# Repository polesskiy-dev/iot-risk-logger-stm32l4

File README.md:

# IoT Risk Data Logger, 
## STM32L4 based

Open source & open hardware project aimed to collect environment data e.g for logistics, cold chain monitoring, last mile delivery, etc.

## Features
TODO

## Firmware docs

[Documentation: Doxygen](https://polesskiy-dev.github.io/iot-risk-logger-stm32l4/)

## Firmware structure
* enclosure - 3D models for enclosure
* hardware - schematics, PCB, BOM
* firmware/iot-risk-logger-stm32l4 - main application
  * libraries - external libraries
  * [app](https://github.com/polesskiy-dev/iot-risk-logger-stm32l4/tree/main/firmware/iot-risk-logger-stm32l4/app) - main application
    * drivers - drivers for peripherals
    * core - actors util functions, core non-threaded modules
    * config - configuration files, list of events and actors    
    * [tasks](https://github.com/polesskiy-dev/iot-risk-logger-stm32l4/tree/main/firmware/iot-risk-logger-stm32l4/app/tasks) - main threads

## Parts video 

https://github.com/polesskiy-dev/iot-risk-logger-stm32l4/assets/5185707/393b0768-925d-4c34-bb85-259de904c167

## Schematics & PCB
[Schematics PDF](hardware/docs/iot-risk-logger-stm32l4.pdf)

## Hardware specifications

|Item|Description|
|-|-|
| MCU | STM32L412 Cortex M4, 80MHz (48), 128K ROM, 40K RAM, TQFP32 |
| Crystal | 32.768kHz |
| Flash | QSPI 64Mbit |
| NFC | ST25DV04K |
| Temperature & Humidity | SHT30-DIS |
| Light | OPT3001 |
| IMU | LIS2DW12 |
| Power | CR2032 3V 235mAh |

## Enclosure
### Assembly

### Developed with
|||
|-|-|
| OS | MacOS, Apple Silicon |
| Schematics & PCB | KiCAD 7.0.0 |
| 3D CAD | Fusion 360 |
| Graphical MCU configure | STM32CubeMX 6.10.0 | 
| IDE | neovim, CLion |
| Hardware debug probe | J-Link EDU Mini 8.08.91 |
| Firmware debug | Segger Ozone 7.94 | 
| Firmware debug analysis | Segger SystemView 3.52 |
| Power analysis | Nordic Power Profiler Kit II |
| Oscilloscope & Logic analyzer | Digilent Analog Discovery 3 |
| Logic analyzer software | Digilent Waveforms | 

## Quick start

After clone, init submodules if you forgot

```bash
git submodule update --init --recursive
```

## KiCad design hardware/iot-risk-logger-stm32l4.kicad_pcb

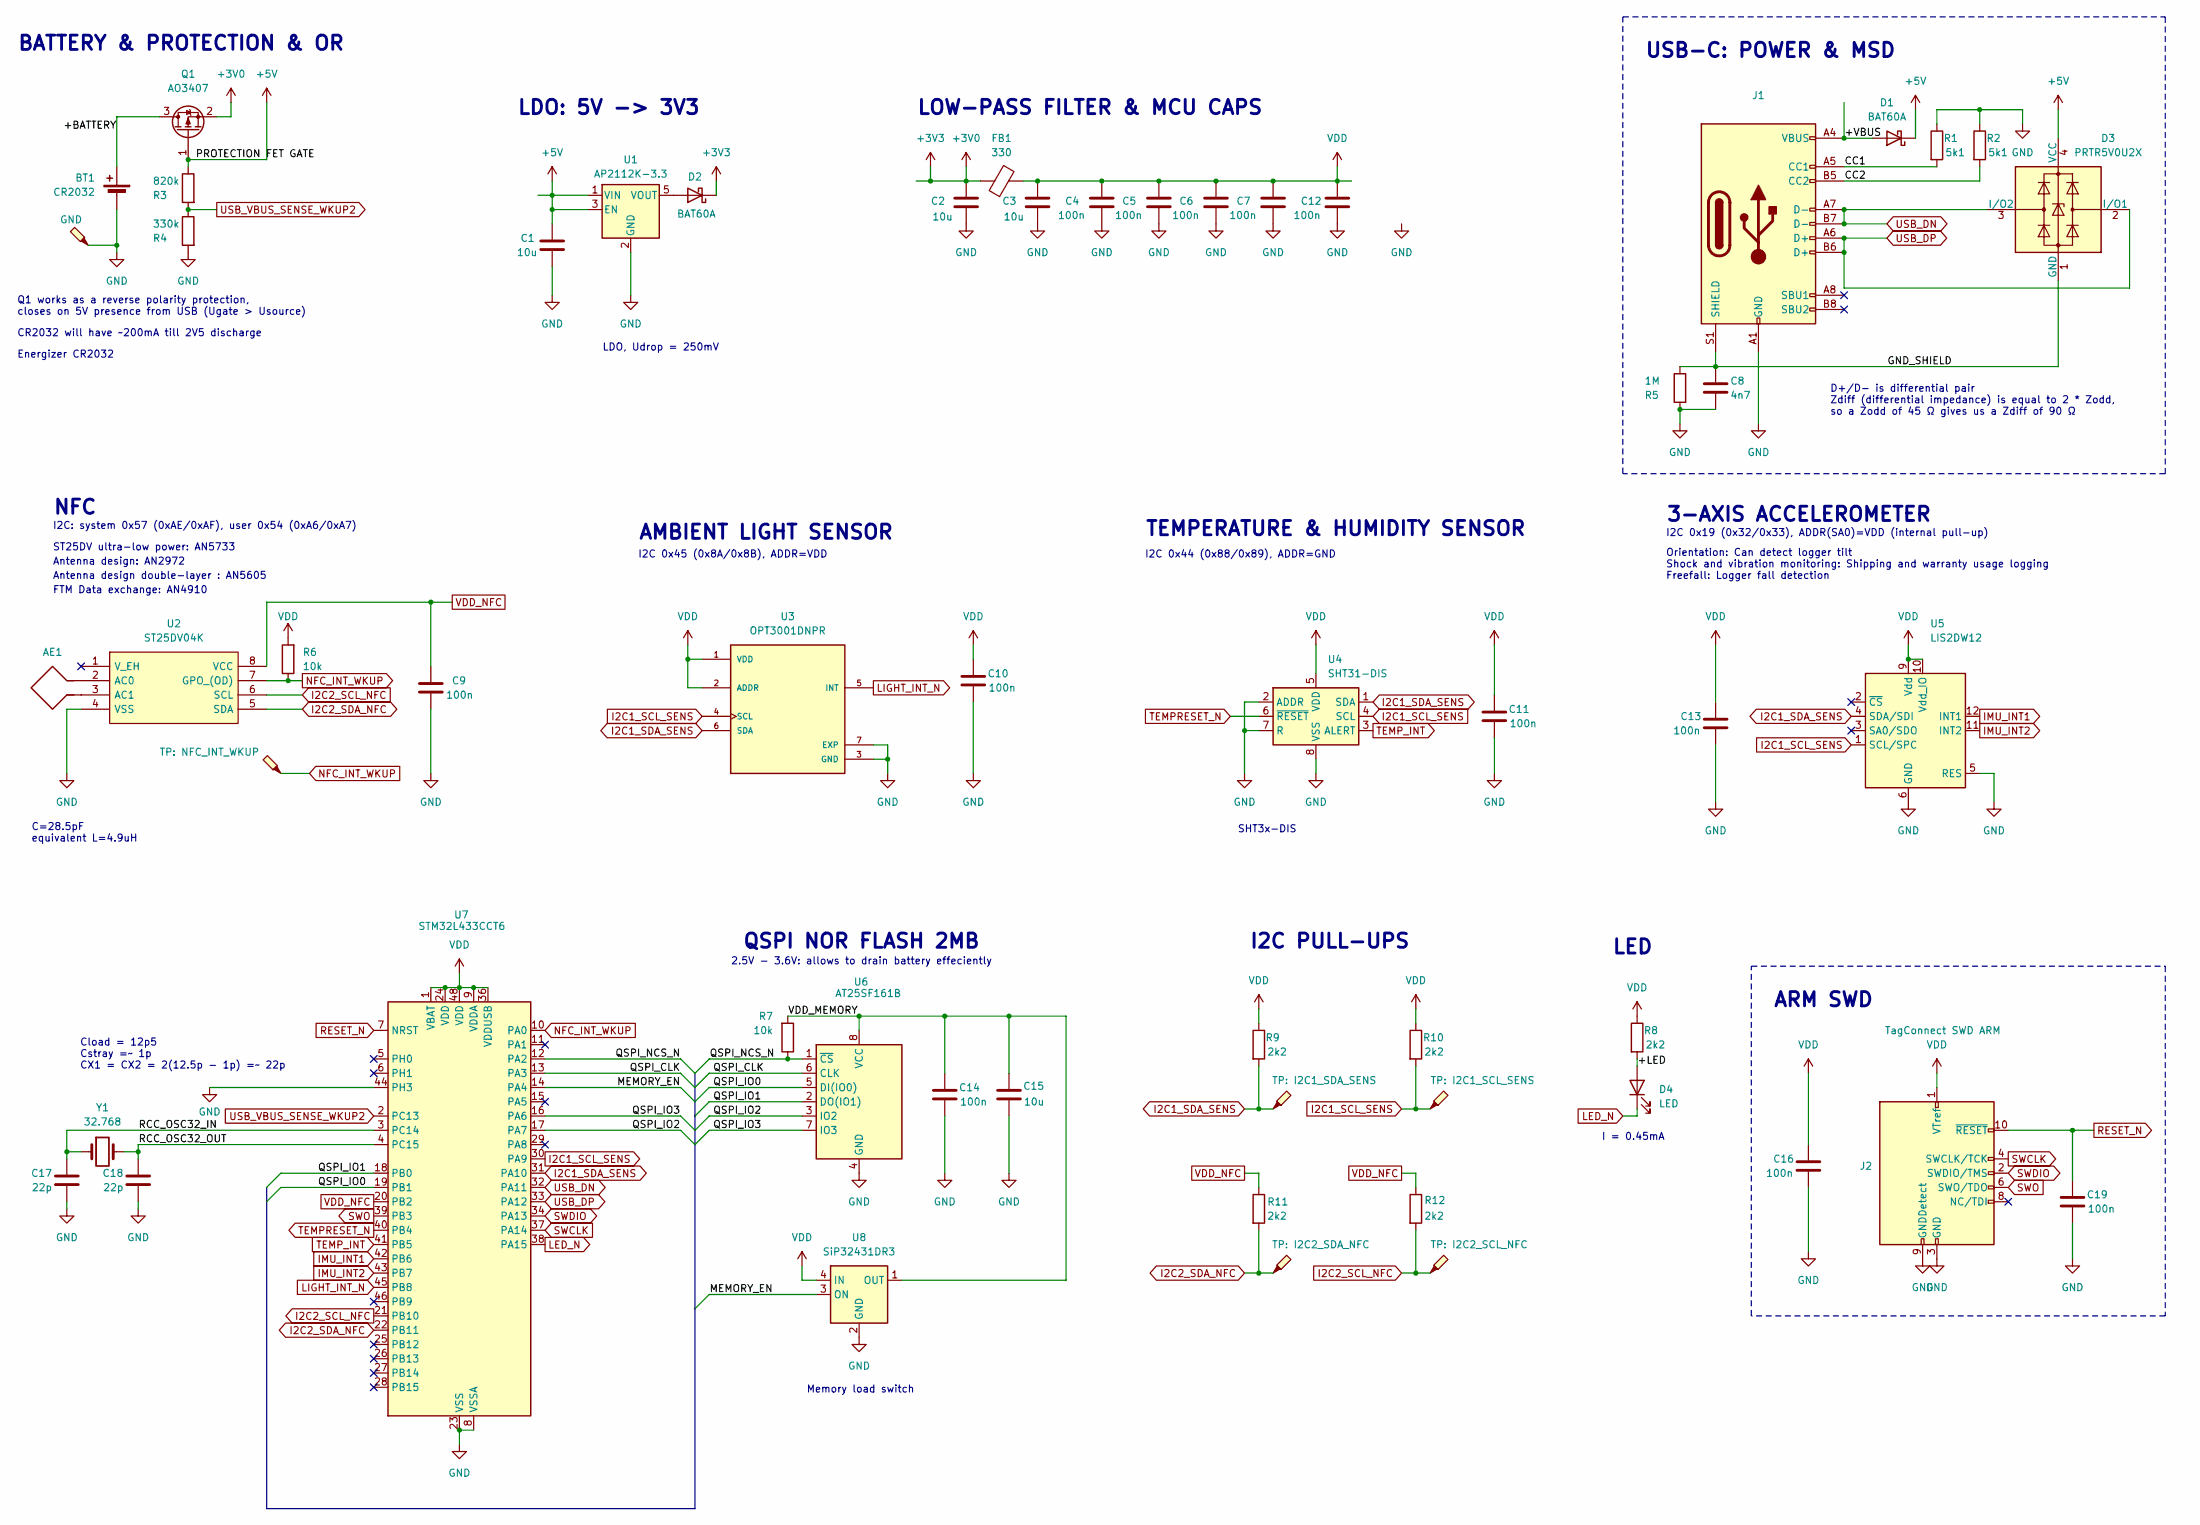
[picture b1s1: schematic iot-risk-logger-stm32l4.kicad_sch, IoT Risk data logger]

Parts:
AE1: Antenna_Loop; NFC_20x40
BT1: CR2032; BatteryHolder_Keystone_3002_1x2032; Mfr. Part # MY-2032-05; LCSC Part # C964829
C1, C2, C3, C15: 10u; C_0805_2012Metric_Pad1.18x1.45mm_HandSolder; Mfr. Part # CL21A106KOQNNNE; LCSC Part # C1713
C4, C5, C6, C7, C9, C10, C11, C12, C13, C14, C16, C19: 100n; C_0603_1608Metric_Pad1.08x0.95mm_HandSolder; Mfr. Part # CL10B104KB8NNNC; LCSC Part # C1591
C8: 4n7; C_0603_1608Metric_Pad1.08x0.95mm_HandSolder; Mfr. Part # CL10B472KB8NNNC; LCSC Part # C1621
C17, C18: 22p; C_0603_1608Metric; Mfr. Part # CL10C220JB8NNNC; LCSC Part # C1653
D1, D2: BAT60A; D_SOD-323_HandSoldering; Mfr. Part # BAT60A; LCSC Part # C5355496
D3: PRTR5V0U2X; SOT-143; Mfr. Part # PRTR5V0U2X; LCSC Part # C2827688
D4: LED; LED_0805_2012Metric_Pad1.15x1.40mm_HandSolder; Mfr. Part # NCD0805G1; LCSC Part # C84260
FB1: 330; L_0805_2012Metric_Pad1.15x1.40mm_HandSolder; Mfr. Part # BLM18SG331TN1D; LCSC Part # C88989
J1: USB Type-C; USB_C_Receptacle_XKB_U262-16XN-4BVC11; Mfr. Part # KH-TYPE-C-16P; LCSC Part # C709357
J2: TagConnect SWD ARM; Tag-Connect_TC2050-IDC-NL_2x05_P1.27mm_Vertical_with_bottom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
Q1: AO3407; SOT-23; Mfr. Part # AO3407; LCSC Part # C2938376
R1, R2: 5k1; R_0603_1608Metric_Pad0.98x0.95mm_HandSolder; Mfr. Part # RC0603JR-075K1L; LCSC Part # C14677
R3: 820k; R_0603_1608Metric_Pad0.98x0.95mm_HandSolder; Mfr. Part # RC0603FR-07820KL; LCSC Part # C141684
R4: 330k; R_0603_1608Metric_Pad0.98x0.95mm_HandSolder; Mfr. Part # RC0603FR-07330KL; LCSC Part # C114618
R5: 1M; R_0603_1608Metric_Pad0.98x0.95mm_HandSolder; Mfr. Part # RC0603JR-071ML; LCSC Part # C107698
R6, R7: 10k; R_0603_1608Metric_Pad0.98x0.95mm_HandSolder; Mfr. Part # RC0603FR-0710KL; LCSC Part # C98220
R8, R9, R10, R11, R12: 2k2; R_0603_1608Metric_Pad0.98x0.95mm_HandSolder; Mfr. Part # RC0603JR-072K2L; LCSC Part # C113303
TP1: GND; TestPoint_Pad_D1.5mm
TP2: TP: NFC_INT_WKUP; TestPoint_Pad_D1.5mm
TP3: TP: I2C1_SDA_SENS; TestPoint_Pad_D1.5mm
TP4: TP: I2C1_SCL_SENS; TestPoint_Pad_D1.5mm
TP5: TP: I2C2_SDA_NFC; TestPoint_Pad_D1.5mm
TP6: TP: I2C2_SCL_NFC; TestPoint_Pad_D1.5mm
U1: AP2112K-3.3; SOT-23-5; Mfr. Part # AP2112K-3.3TRG1; LCSC Part # C51118
U2: ST25DV04K; TSSOP-8_4.4x3mm_P0.65mm; Mfr. Part # ST25DV04K-IER6T3; LCSC Part # C2654816
U3: OPT3001DNPR; SON65P200X200X65-7N; Mfr. Part # OPT3001DNPR; LCSC Part # C90462
U4: SHT31-DIS; Sensirion_DFN-8-1EP_2.5x2.5mm_P0.5mm_EP1.1x1.7mm; Mfr. Part # SHT31-DIS-B2.5kS; LCSC Part # C80862
U5: LIS2DW12; LGA-12_2x2mm_P0.5mm; Mfr. Part # LIS2DW12TR; LCSC Part # C189624
U6: AT25SF161B; SOIC-8_3.9x4.9mm_P1.27mm; Mfr. Part # AT25SF161B-SSHD-B; LCSC Part # C5555633
U7: STM32L433CCT6; LQFP-48_7x7mm_P0.5mm; Mfr. Part # STM32L433CCT6; LCSC Part # C110061
U8: SiP32431DR3; SOT-363_SC-70-6; Mfr. Part # SIP32431DR3-T1GE3; LCSC Part # C141606
Y1: 32.768; Crystal_SMD_EuroQuartz_EQ161-2Pin_3.2x1.5mm; Mfr. Part # SC-32S32.768kHz20PPM12.5pF; LCSC Part # C97606

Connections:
+3V0: C2.1, D2.1 (K), FB1.1, Q1.2 (S)
+5V: C1.1, D1.1 (K), D3.4 (VCC), Q1.1 (G), R3.1, U1.1 (VIN), U1.3 (EN)
/+BATTERY: BT1.1 (+), Q1.3 (D)
/+LED: D4.2 (A), R8.2
/+VBUS: D1.2 (A), J1.A4 (VBUS), J1.A9 (VBUS), J1.B4 (VBUS), J1.B9 (VBUS)
/CC1: J1.A5 (CC1), R1.2
/CC2: J1.B5 (CC2), R2.2
/GND_SHIELD: C8.1, D3.1 (GND), J1.S1 (SHIELD), R5.1
/MEMORY_EN: U7.14 (PA4), U8.3 (ON)
/QSPI_CLK: U6.6 (CLK), U7.13 (PA3)
/QSPI_IO0: U6.5 (DI(IO0)), U7.19 (PB1)
/QSPI_IO1: U6.2 (DO(IO1)), U7.18 (PB0)
/QSPI_IO2: U6.3 (IO2), U7.17 (PA7)
/QSPI_IO3: U6.7 (IO3), U7.16 (PA6)
/QSPI_NCS_N: R7.1, U6.1 (~CS), U7.12 (PA2)
/RCC_OSC32_IN: C17.1, U7.3 (PC14), Y1.1
/RCC_OSC32_OUT: C18.1, U7.4 (PC15), Y1.2
/VDD_MEMORY: C14.1, C15.1, R7.2, U6.8 (VCC), U8.1 (OUT)
GND: BT1.2 (-), C1.2, C2.2, C3.2, C4.2, C5.2, C6.2, C7.2, C8.2, C9.2, C10.2, C11.2, C12.2, C13.2, C14.2, C15.2, C16.2, C17.2, C18.2, C19.2, J1.A1 (GND), J1.A12 (GND), J1.B1 (GND), J1.B12 (GND), J2.3 (GND), J2.5 (GND), J2.9 (GNDDetect), R1.1, R2.1, R4.2, R5.2, TP1.1, U1.2 (GND), U2.4 (VSS), U3.3 (GND), U3.7 (EXP), U4.2 (ADDR), U4.7 (R), U4.8 (VSS), U4.9 (VSS), U5.5 (RES), U5.6 (GND), U5.7 (GND), U5.8 (GND), U6.4 (GND), U7.8 (VSSA), U7.23 (VSS), U7.35 (VSS), U7.44 (PH3), U7.47 (VSS), U8.2 (GND), U8.5 (GND)
I2C1_SCL_SENS: R10.2, TP4.1, U3.4 (SCL), U4.4 (SCL), U5.1 (SCL/SPC), U7.30 (PA9)
I2C1_SDA_SENS: R9.2, TP3.1, U3.6 (SDA), U4.1 (SDA), U5.4 (SDA/SDI), U7.31 (PA10)
I2C2_SCL_NFC: R12.2, TP6.1, U2.6 (SCL), U7.21 (PB10)
I2C2_SDA_NFC: R11.2, TP5.1, U2.5 (SDA), U7.22 (PB11)
IMU_INT1: U5.12 (INT1), U7.42 (PB6)
IMU_INT2: U5.11 (INT2), U7.43 (PB7)
LED_N: D4.1 (K), U7.38 (PA15)
LIGHT_INT_N: U3.5 (INT), U7.45 (PB8)
NFC_INT_WKUP: R6.1, TP2.1, U2.7 (GPO_(OD)), U7.10 (PA0)
unnamed: D2.2 (A), U1.5 (VOUT)
unnamed: AE1.2, U2.2 (AC0)
unnamed: AE1.1, U2.3 (AC1)
RESET_N: C19.1, J2.10 (~RESET), U7.7 (NRST)
SWCLK: J2.4 (SWCLK/TCK), U7.37 (PA14)
SWDIO: J2.2 (SWDIO/TMS), U7.34 (PA13)
SWO: J2.6 (SWO/TDO), U7.39 (PB3)
TEMPRESET_N: U4.6 (~RESET), U7.40 (PB4)
TEMP_INT: U4.3 (ALERT), U7.41 (PB5)
USB_DN: D3.3 (I/O2), J1.A7 (D-), J1.B7 (D-), U7.32 (PA11)
USB_DP: D3.2 (I/O1), J1.A6 (D+), J1.B6 (D+), U7.33 (PA12)
USB_VBUS_SENSE_WKUP2: R3.2, R4.1, U7.2 (PC13)
VDD: C3.1, C4.1, C5.1, C6.1, C7.1, C10.1, C11.1, C12.1, C13.1, C16.1, FB1.2, J2.1 (VTref), R6.2, R8.1, R9.1, R10.1, U3.1 (VDD), U3.2 (ADDR), U4.5 (VDD), U5.9 (Vdd), U5.10 (Vdd_IO), U7.1 (VBAT), U7.9 (VDDA), U7.24 (VDD), U7.36 (VDDUSB), U7.48 (VDD), U8.4 (IN)
VDD_NFC: C9.1, R11.1, R12.1, U2.8 (VCC), U7.20 (PB2)

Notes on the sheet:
BATTERY & PROTECTION & OR
CR2032 will have ~200mA till 2V5 discharge
С=28.5pF equivalent L=4.9uH
TEMPERATURE & HUMIDITY SENSOR
ST25DV ultra-low power: AN5733
LDO, Udrop = 250mV
LED
Q1 works as a reverse polarity protection, closes on 5V presence from USB (Ugate > Usource)
QSPI NOR FLASH 2MB
Antenna design double-layer : AN5605
FTM Data exchange: AN4910
Memory load switch
3-AXIS ACCELEROMETER
D+/D- is differential pair Zdiff (differential impedance) is equal to 2 * Zodd, so a Zodd of 45 Ω gives us a Zdiff of 90 Ω
I2C 0x44 (0x88/0x89), ADDR=GND
2.5V - 3.6V: allows to drain battery effeciently
I2C: system 0x57 (0xAE/0xAF), user 0x54 (0xA6/0xA7)
Antenna design: AN2972
Cload = 12p5 Cstray =~ 1p CX1 = CX2 = 2(12.5p - 1p) =~ 22p
ARM SWD
I2C 0x19 (0x32/0x33), ADDR(SA0)=VDD (internal pull-up)
USB-C: POWER & MSD
AMBIENT LIGHT SENSOR
SHT3x-DIS
Orientation: Can detect logger tilt Shock and vibration monitoring: Shipping and warranty usage logging Freefall: Logger fall detection
I = 0.45mA
I2C 0x45 (0x8A/0x8B), ADDR=VDD
LOW-PASS FILTER & MCU CAPS
I2C PULL-UPS
Energizer CR2032
NFC
LDO: 5V -> 3V3

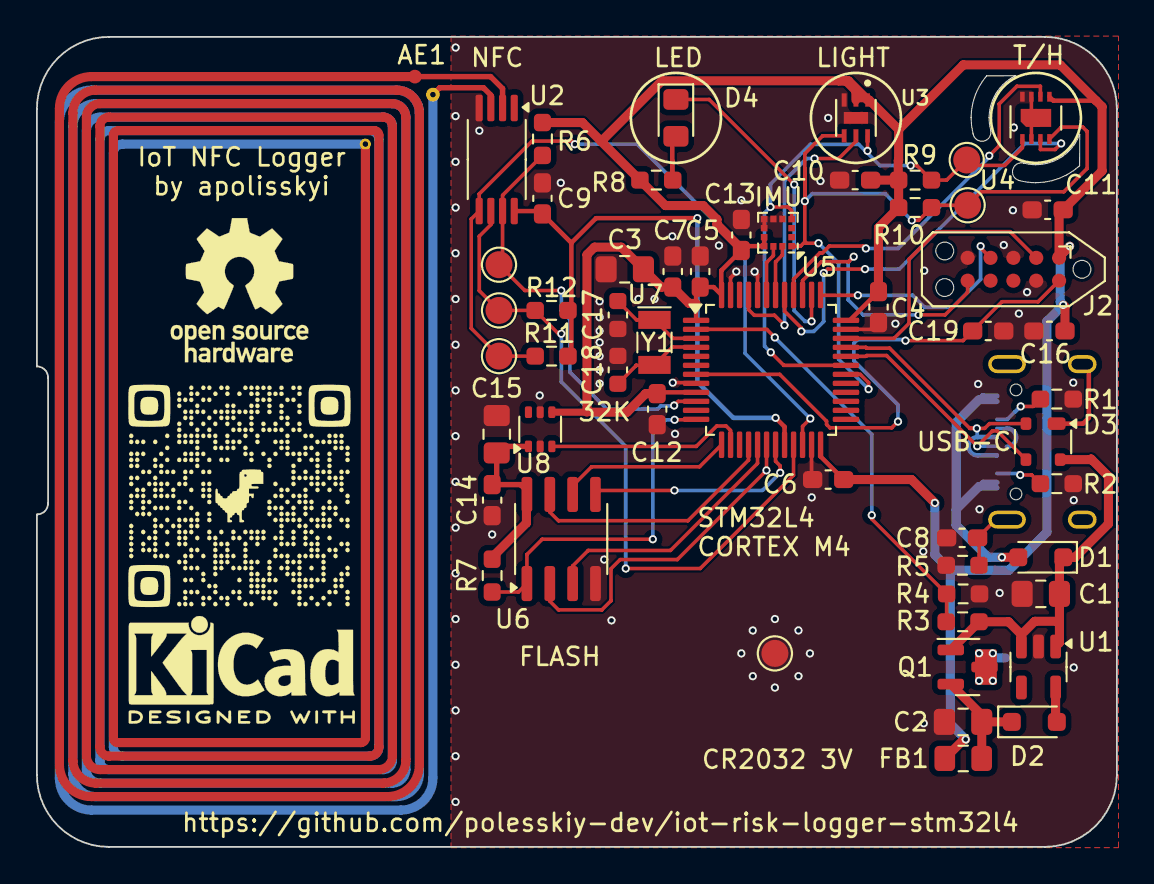
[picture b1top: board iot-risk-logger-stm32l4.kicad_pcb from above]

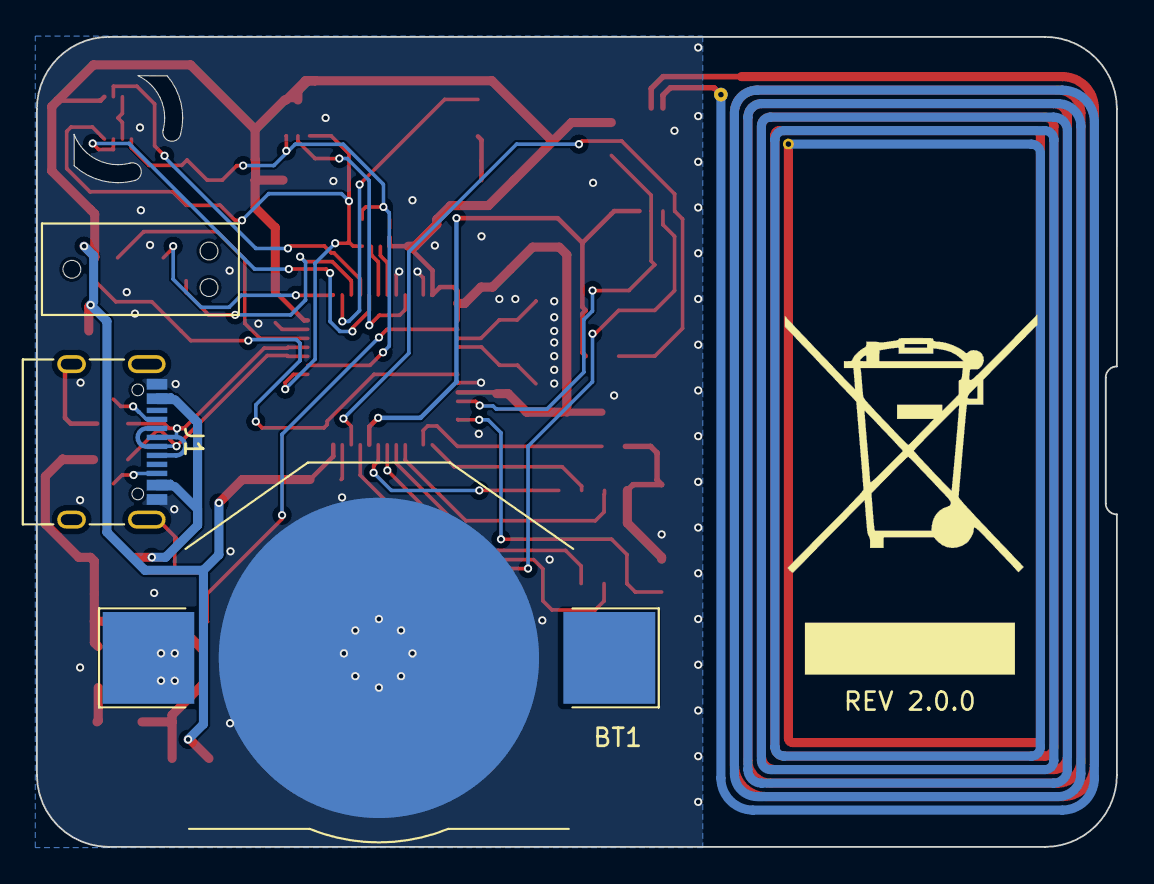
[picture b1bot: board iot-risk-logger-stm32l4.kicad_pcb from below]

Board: 2 copper layers, 60.0 x 45.0 mm, 59 parts (3 on the bottom side), 42 nets.

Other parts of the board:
REF1: KiCad-Logo2_5mm_SilkScreen
REF2: OSHW-Logo_7.5x8mm_SilkScreen
REF3: WEEE-Logo_14x20mm_SilkScreen

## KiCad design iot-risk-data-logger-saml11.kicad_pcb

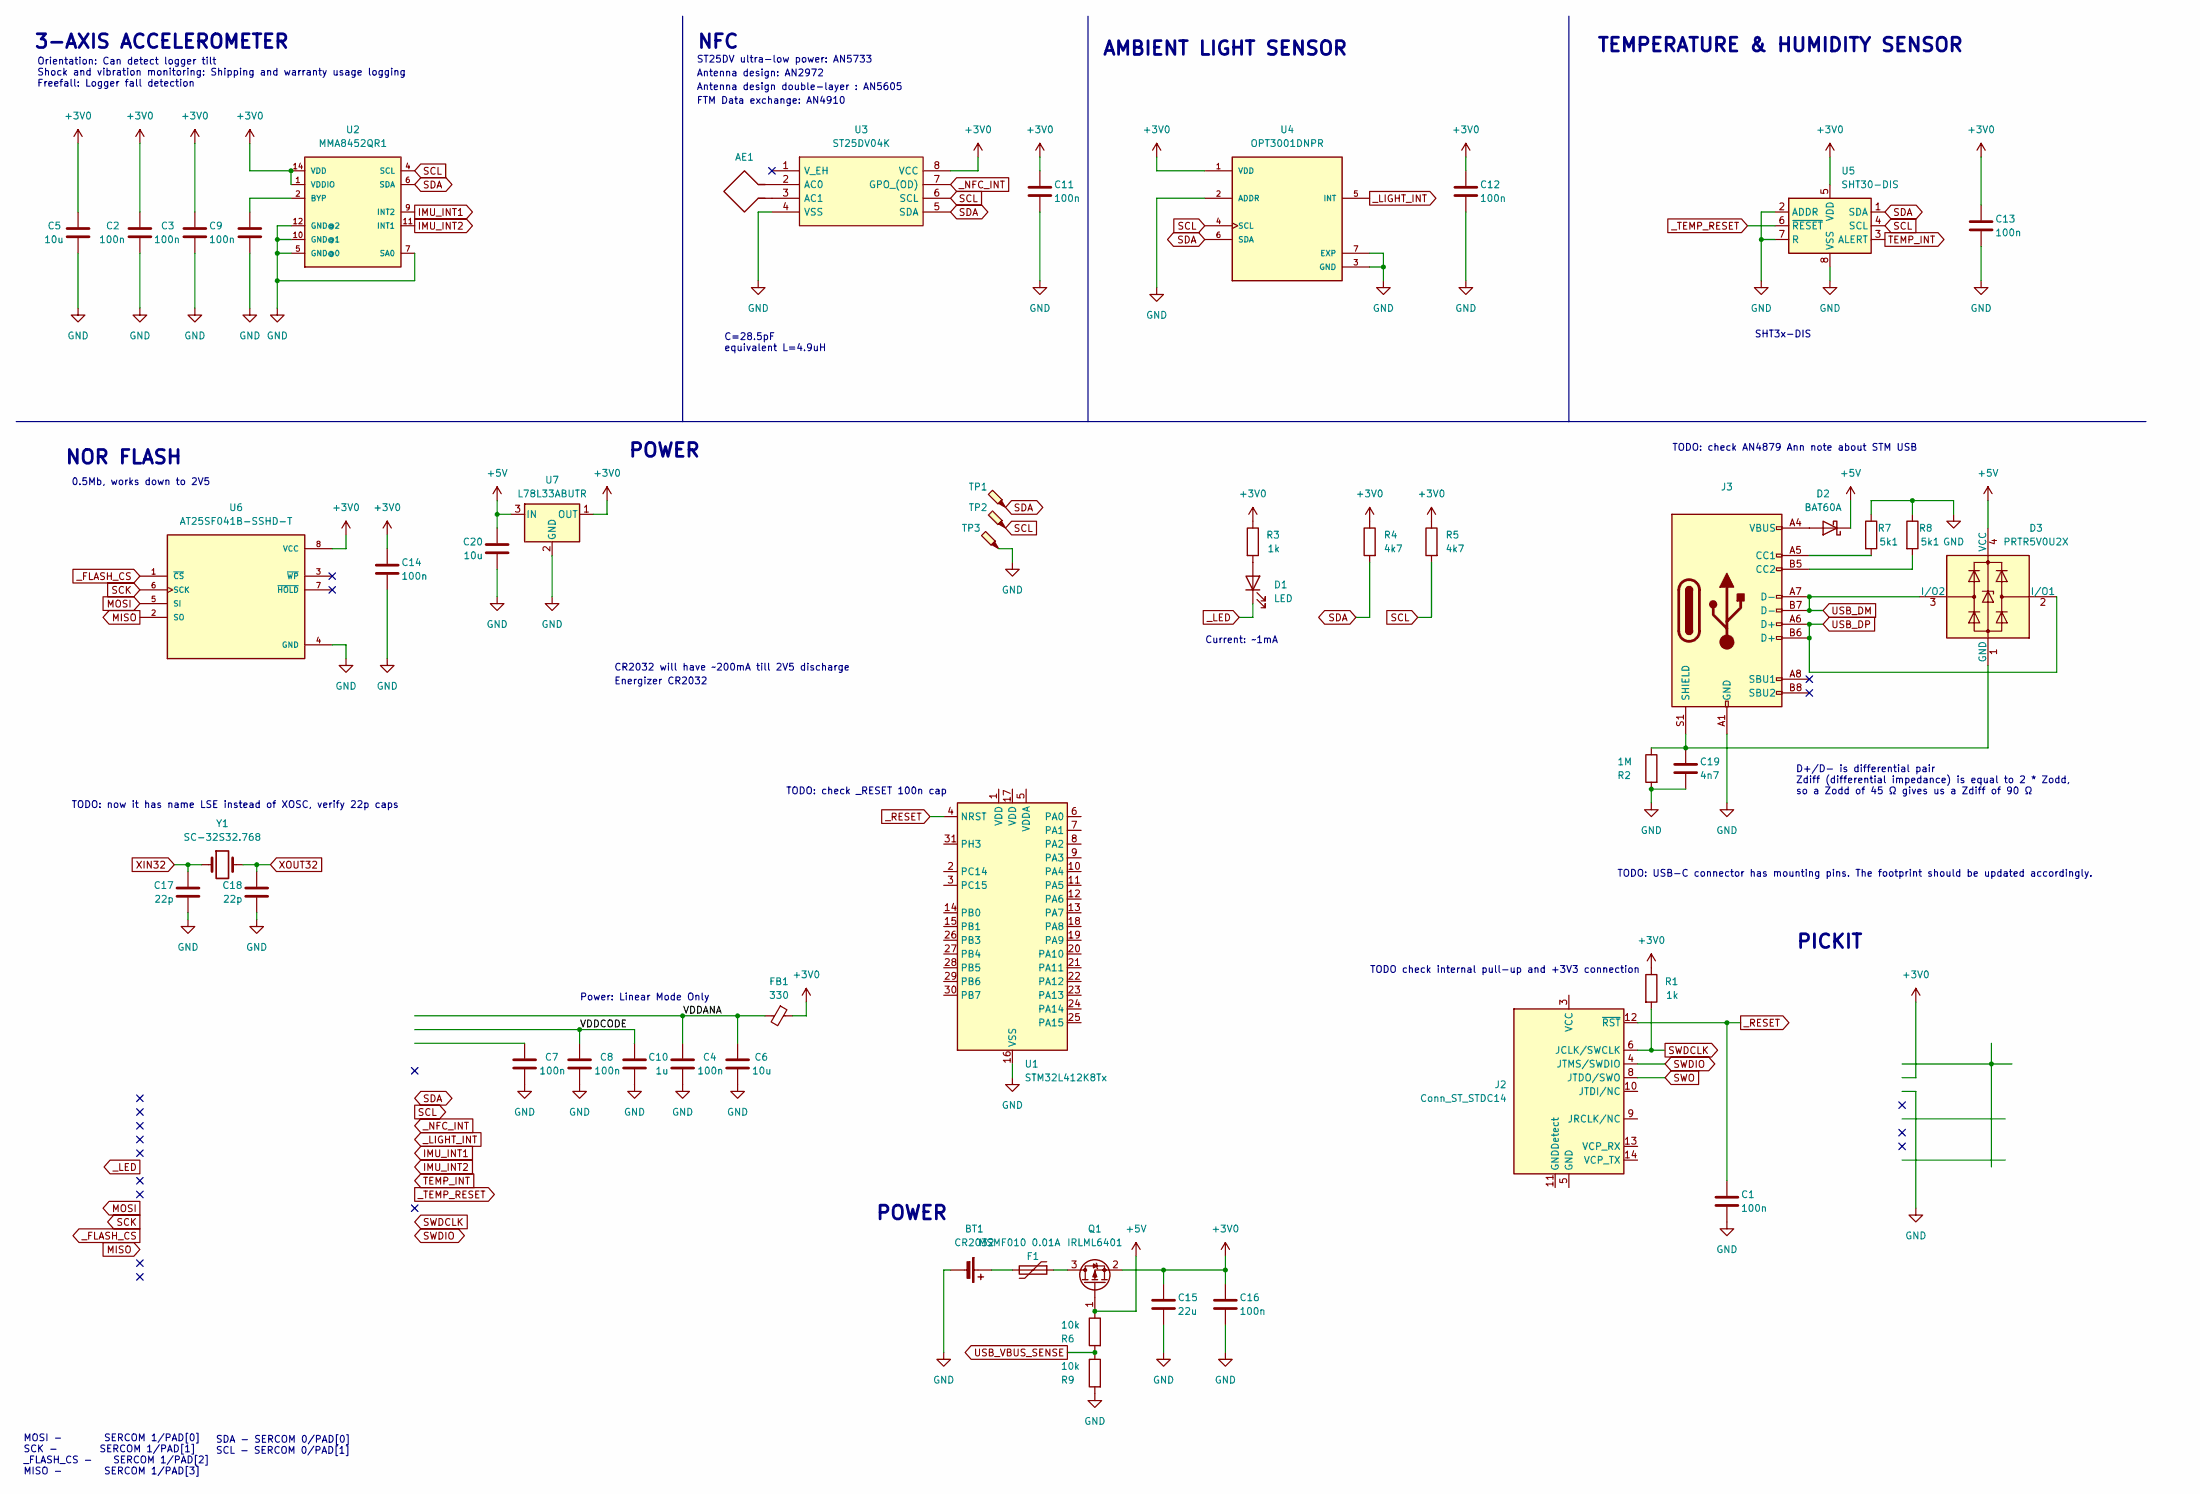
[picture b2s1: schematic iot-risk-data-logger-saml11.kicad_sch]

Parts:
AE1: Antenna_Loop; ANT_NFC_30x40
BT1: CR2032; BatteryHolder_Keystone_3002_1x2032; Part MY-2032-05; LCSC Part C964829
C1, C2, C3, C4, C7, C8, C9, C11, C12, C13, C14, C16: 100n; C_0805_2012Metric_Pad1.18x1.45mm_HandSolder; Part CL21B104KBCNNNC; LCSC Part C1711
C5, C6, C20: 10u; C_0805_2012Metric_Pad1.18x1.45mm_HandSolder; Part CL21A106KOQNNNE; LCSC Part C1713
C10: 1u; C_0805_2012Metric_Pad1.18x1.45mm_HandSolder; Part CL21A105KACLNNC; LCSC Part C2932475
C15: 22u; C_1206_3216Metric_Pad1.33x1.80mm_HandSolder; Part CL31A226KAHNNNE; LCSC Part C12891
C17, C18: 22p; C_0805_2012Metric_Pad1.18x1.45mm_HandSolder; Part CL21C220JBANNNC; LCSC Part C1804
C19: 4n7; C_0805_2012Metric_Pad1.18x1.45mm_HandSolder; Part CL21B472KBANNNC; LCSC Part C50131
D1: LED; LED_0805_2012Metric_Pad1.15x1.40mm_HandSolder; Part NCD0805G1; LCSC Part C84260
D2: BAT60A; D_SOD-323_HandSoldering; Part BAT60A; LCSC Part C5355496
D3: PRTR5V0U2X; SOT-143; Part PRTR5V0U2X; LCSC Part C2827688
F1: MSMF010 0.01A; Fuse_1812_4532Metric_Pad1.30x3.40mm_HandSolder; Part MF-MSMF010-2; LCSC Part C12430
FB1: 330; R_0805_2012Metric_Pad1.20x1.40mm_HandSolder; Part BLM21PG331SN1D; LCSC Part C47130
J2: Conn_ST_STDC14; PinHeader_2x07_P1.27mm_Vertical_SMD
J3: USB Type-C; USB_C_Receptacle_XKB_U262-16XN-4BVC11; Part KH-TYPE-C-16P; LCSC Part C709357
Q1: IRLML6401; SOT-23; Part IRLML6401TRPBF; LCSC Part C3034
R1, R3: 1k; R_0805_2012Metric_Pad1.20x1.40mm_HandSolder; Part RC0805FR-071KL; LCSC Part C95781
R2: 1M; R_0805_2012Metric_Pad1.20x1.40mm_HandSolder; Part RC0805FR-071ML; LCSC Part C107700
R4, R5: 4k7; R_0805_2012Metric_Pad1.20x1.40mm_HandSolder; Part RC0805FR-074K7L; LCSC Part C60816
R6, R9: 10k; R_0805_2012Metric_Pad1.20x1.40mm_HandSolder; Part RC0805FR-0710KL; LCSC Part C84376
R7, R8: 5k1; R_0805_2012Metric_Pad1.20x1.40mm_HandSolder; Part RC0805FR-075K1L; LCSC Part C84375
TP1, TP2, TP3: TestPoint_Probe; TestPoint_THTPad_D1.5mm_Drill0.7mm
U1: STM32L412K8Tx; LQFP-32_7x7mm_P0.8mm
U2: MMA8452QR1; XDCR_MMA8452QR1; Part MMA8452QR1; LCSC Part C11360
U3: ST25DV04K; TSSOP-8_4.4x3mm_P0.65mm; Part ST25DV04K-IER6T3; LCSC Part C2654816
U4: OPT3001DNPR; SON65P200X200X65-7N; Part OPT3001DNPR; LCSC Part C90462
U5: SHT30-DIS; Sensirion_DFN-8-1EP_2.5x2.5mm_P0.5mm_EP1.1x1.7mm; Part SHT30-DIS-B10KS; LCSC Part C2687423
U6: AT25SF041B-SSHD-T; SOIC-8_3.9x4.9mm_P1.27mm; Part AT25SF041B-SSHD-T; LCSC Part C5127618
U7: L78L33ABUTR; SOT-89-3_Handsoldering; Part L78L33ABUTR; LCSC Part C81362
Y1: SC-32S32.768; Crystal_SMD_EuroQuartz_EQ161-2Pin_3.2x1.5mm_HandSoldering; Part SC-32S32.768kHz20PPM12.5pF; LCSC Part C97606

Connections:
+3V0: C2.1, C3.1, C5.1, C11.1, C12.1, C13.1, C14.1, C15.1, C16.1, FB1.1, Q1.2 (S), R1.1, R3.1, R4.1, R5.1, U2.1 (VDDIO), U2.14 (VDD), U3.8 (VCC), U4.1 (VDD), U5.5 (VDD), U6.8 (VCC), U7.1 (OUT)
+5V: C20.1, D2.1 (K), D3.4 (VCC), Q1.1 (G), R6.1, U7.3 (IN)
/VDDANA: C4.1, C6.1, FB1.2
/VDDCODE: C8.1, C10.1
GND: BT1.2 (-), C1.2, C2.2, C3.2, C4.2, C5.2, C6.2, C7.2, C8.2, C9.2, C10.2, C11.2, C12.2, C13.2, C14.2, C15.2, C16.2, C17.2, C18.2, C19.2, C20.2, J3.A1 (GND), J3.A12 (GND), J3.B1 (GND), J3.B12 (GND), R2.2, R7.1, R8.1, R9.2, TP3.1, U1.16 (VSS), U1.32 (VSS), U2.5 (GND@0), U2.7 (SA0), U2.10 (GND@1), U2.12 (GND@2), U3.4 (VSS), U4.2 (ADDR), U4.3 (GND), U4.7 (EXP), U5.2 (ADDR), U5.7 (R), U5.8 (VSS), U5.9 (VSS), U6.4 (GND), U7.2 (GND)
IMU_INT1: U2.9 (INT2)
IMU_INT2: U2.11 (INT1)
MISO: U6.2 (SO)
MOSI: U6.5 (SI)
unnamed: BT1.1 (+), F1.2
unnamed: D1.2 (A), R3.2
unnamed: D2.2 (A), J3.A4 (VBUS), J3.A9 (VBUS), J3.B4 (VBUS), J3.B9 (VBUS)
unnamed: C19.1, D3.1 (GND), J3.S1 (SHIELD), R2.1
unnamed: J2.5 (GND), J2.7 (GND)
unnamed: J3.A5 (CC1), R7.2
unnamed: J3.B5 (CC2), R8.2
unnamed: F1.1, Q1.3 (D)
unnamed: C9.1, U2.2 (BYP)
unnamed: AE1.2, U3.2 (AC0)
unnamed: AE1.1, U3.3 (AC1)
SCK: U6.6 (SCK)
SCL: R5.2, TP2.1, U2.4 (SCL), U3.6 (SCL), U4.4 (SCL), U5.4 (SCL)
SDA: R4.2, TP1.1, U2.6 (SDA), U3.5 (SDA), U4.6 (SDA), U5.1 (SDA)
SWDCLK: J2.6 (JCLK/SWCLK), R1.2
SWDIO: J2.4 (JTMS/SWDIO)
SWO: J2.8 (JTDO/SWO)
TEMP_INT: U5.3 (ALERT)
USB_DM: D3.3 (I/O2), J3.A7 (D-), J3.B7 (D-)
USB_DP: D3.2 (I/O1), J3.A6 (D+), J3.B6 (D+)
USB_VBUS_SENSE: R6.2, R9.1
XIN32: C17.1, Y1.1
XOUT32: C18.1, Y1.2
_FLASH_CS: U6.1 (~CS)
_LED: D1.1 (K)
_LIGHT_INT: U4.5 (INT)
_NFC_INT: U3.7 (GPO_(OD))
_RESET: C1.1, J2.12 (~RST), U1.4 (NRST)
_TEMP_RESET: U5.6 (~RESET)

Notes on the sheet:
Current: ~1mA
POWER
CR2032 will have ~200mA till 2V5 discharge
С=28.5pF equivalent L=4.9uH
MOSI - SERCOM 1/PAD[0] SCK - SERCOM 1/PAD[1] _FLASH_CS - SERCOM 1/PAD[2] MISO - SERCOM 1/PAD[3]
TEMPERATURE & HUMIDITY SENSOR
SDA - SERCOM 0/PAD[0] SCL - SERCOM 0/PAD[1]
ST25DV ultra-low power: AN5733
NOR FLASH
TODO check internal pull-up and +3V3 connection
Antenna design double-layer : AN5605
FTM Data exchange: AN4910
3-AXIS ACCELEROMETER
D+/D- is differential pair Zdiff (differential impedance) is equal to 2 * Zodd, so a Zodd of 45 Ω gives us a Zdiff of 90 Ω
Antenna design: AN2972
TODO: now it has name LSE instead of XOSC, verify 22p caps
TODO: check _RESET 100n cap
Power: Linear Mode Only
0.5Mb, works down to 2V5
TODO: USB-C connector has mounting pins. The footprint should be updated accordingly.
AMBIENT LIGHT SENSOR
TODO: check AN4879 Ann note about STM USB
SHT3x-DIS
PICKIT
Orientation: Can detect logger tilt Shock and vibration monitoring: Shipping and warranty usage logging Freefall: Logger fall detection
Energizer CR2032
NFC

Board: 2 copper layers, 49 parts (3 on the bottom side), 23 nets, no tracks yet.

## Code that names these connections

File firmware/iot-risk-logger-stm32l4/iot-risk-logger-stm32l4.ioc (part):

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Mcu.Name=STM32L433C(B-C)Tx
Mcu.Package=LQFP48
Mcu.UserName=STM32L433CBTx
PA0.GPIOParameters=GPIO_PuPd,GPIO_Label,GPIO_ModeDefaultEXTI
PA0.GPIO_Label=NFC_INT_WKUP
PA0.GPIO_ModeDefaultEXTI=GPIO_MODE_IT_FALLING
PA0.GPIO_PuPd=GPIO_NOPULL
PA0.Signal=GPXTI0
PA1.GPIOParameters=GPIO_Label
PA1.GPIO_Label=PA1_Disabled
PA1.Signal=GPIO_Analog
PA10.GPIOParameters=GPIO_Label
PA10.GPIO_Label=I2C1_SDA_SENS
PA10.Mode=I2C
PA10.Signal=I2C1_SDA
PA11.GPIOParameters=GPIO_Label
PA11.GPIO_Label=USB_DM_N
PA11.Mode=Device
PA11.Signal=USB_DM
PA12.GPIOParameters=GPIO_Label
PA12.GPIO_Label=USB_DP_P
PA12.Mode=Device
PA12.Signal=USB_DP
PA13\ (JTMS-SWDIO).GPIOParameters=GPIO_Label
PA13\ (JTMS-SWDIO).GPIO_Label=SWDIO
PA13\ (JTMS-SWDIO).Mode=Trace_Asynchronous_SW
PA13\ (JTMS-SWDIO).Signal=SYS_JTMS-SWDIO
PA14\ (JTCK-SWCLK).GPIOParameters=GPIO_Label
PA14\ (JTCK-SWCLK).GPIO_Label=SWCLK
PA14\ (JTCK-SWCLK).Mode=Trace_Asynchronous_SW
PA14\ (JTCK-SWCLK).Signal=SYS_JTCK-SWCLK
PA15\ (JTDI).GPIOParameters=PinState,GPIO_PuPd,GPIO_Label,GPIO_ModeDefaultOutputPP
PA15\ (JTDI).GPIO_Label=LED_N
PA15\ (JTDI).GPIO_ModeDefaultOutputPP=GPIO_MODE_OUTPUT_OD
PA15\ (JTDI).GPIO_PuPd=GPIO_NOPULL
PA15\ (JTDI).PinState=GPIO_PIN_SET
PA15\ (JTDI).Signal=GPIO_Output
PA2.Mode=Single Bank 1
PA2.Signal=QUADSPI_BK1_NCS
PA3.Mode=Single Bank 1
PA3.Signal=QUADSPI_CLK
PA4.GPIOParameters=PinState,GPIO_Label
PA4.GPIO_Label=MEMORY_EN_N
PA4.PinState=GPIO_PIN_SET
PA4.Signal=GPIO_Output
PA5.GPIOParameters=GPIO_Label
PA5.GPIO_Label=PA5_Disabled
PA5.Signal=GPIO_Analog
PA6.Mode=Single Bank 1
PA6.Signal=QUADSPI_BK1_IO3
PA7.Mode=Single Bank 1
PA7.Signal=QUADSPI_BK1_IO2
PA8.GPIOParameters=GPIO_Label
PA8.GPIO_Label=PA8_Disabled
PA8.Signal=GPIO_Analog
PA9.GPIOParameters=GPIO_Label
PA9.GPIO_Label=I2C1_SCL_SENS
PA9.Mode=I2C
PA9.Signal=I2C1_SCL
PB0.Mode=Single Bank 1
PB0.Signal=QUADSPI_BK1_IO1
PB1.Mode=Single Bank 1
PB1.Signal=QUADSPI_BK1_IO0
PB10.GPIOParameters=GPIO_Label
PB10.GPIO_Label=I2C2_SCL_NFC
PB10.Mode=I2C
PB10.Signal=I2C2_SCL
PB11.GPIOParameters=GPIO_Label
PB11.GPIO_Label=I2C2_SDA_NFC
PB11.Mode=I2C
PB11.Signal=I2C2_SDA
PB12.GPIOParameters=GPIO_Label
PB12.GPIO_Label=PB12_Disabled
PB12.Signal=GPIO_Analog
PB13.GPIOParameters=GPIO_Label
PB13.GPIO_Label=PB13_Disabled
PB13.Signal=GPIO_Analog
PB14.GPIOParameters=GPIO_Label
PB14.GPIO_Label=PB14_Disabled
PB14.Signal=GPIO_Analog
PB15.GPIOParameters=GPIO_Label
PB15.GPIO_Label=PB15_Disabled
PB15.Signal=GPIO_Analog
PB2.GPIOParameters=GPIO_Label
PB2.GPIO_Label=VDD_NFC
PB2.Signal=GPIO_Output
PB3\ (JTDO-TRACESWO).GPIOParameters=GPIO_Label
PB3\ (JTDO-TRACESWO).GPIO_Label=SWO
PB3\ (JTDO-TRACESWO).Mode=Trace_Asynchronous_SW
PB3\ (JTDO-TRACESWO).Signal=SYS_JTDO-SWO
PB4\ (NJTRST).GPIOParameters=PinState,GPIO_PuPd,GPIO_Label,GPIO_ModeDefaultOutputPP
PB4\ (NJTRST).GPIO_Label=TEMP_RESET_N
PB4\ (NJTRST).GPIO_ModeDefaultOutputPP=GPIO_MODE_OUTPUT_OD
PB4\ (NJTRST).GPIO_PuPd=GPIO_NOPULL
PB4\ (NJTRST).PinState=GPIO_PIN_SET
PB4\ (NJTRST).Signal=GPIO_Output
PB5.GPIOParameters=GPIO_Label
PB5.GPIO_Label=TEMP_INT
PB5.Signal=GPXTI5
PB6.GPIOParameters=GPIO_Label
PB6.GPIO_Label=IMU_INT1
PB6.Signal=GPXTI6
PB7.GPIOParameters=GPIO_Label
PB7.GPIO_Label=IMU_INT2
PB7.Signal=GPXTI7
PB8.GPIOParameters=GPIO_PuPd,GPIO_Label,GPIO_ModeDefaultEXTI
PB8.GPIO_Label=LIGHT_INT_N
PB8.GPIO_ModeDefaultEXTI=GPIO_MODE_IT_FALLING
PB8.GPIO_PuPd=GPIO_PULLUP
PB8.Signal=GPXTI8
PB9.GPIOParameters=GPIO_Label
PB9.GPIO_Label=PB9_Disabled
PB9.Signal=GPIO_Analog
PC13.GPIOParameters=GPIO_Label
PC13.GPIO_Label=USB_VBUS_SENSE_WKUP2
PC13.Signal=GPXTI13
PC14-OSC32_IN\ (PC14).Mode=LSE-External-Oscillator
PC14-OSC32_IN\ (PC14).Signal=RCC_OSC32_IN
PC15-OSC32_OUT\ (PC15).Mode=LSE-External-Oscillator
PC15-OSC32_OUT\ (PC15).Signal=RCC_OSC32_OUT
PH0-OSC_IN\ (PH0).GPIOParameters=GPIO_Label
PH0-OSC_IN\ (PH0).GPIO_Label=PH0_Disabled
PH0-OSC_IN\ (PH0).Signal=GPIO_Analog
PH1-OSC_OUT\ (PH1).GPIOParameters=GPIO_Label
PH1-OSC_OUT\ (PH1).GPIO_Label=PH1_Disabled
PH1-OSC_OUT\ (PH1).Signal=GPIO_Analog
PH3-BOOT0.GPIOParameters=GPIO_Label
PH3-BOOT0.GPIO_Label=PH3-BOOT0-Disabled
PH3-BOOT0.Signal=GPIO_Analog
RCC.HSE_VALUE=8000000
RCC.SYSCLKFreq_VALUE=80000000
RCC.SYSCLKSource=RCC_SYSCLKSOURCE_PLLCLK
board=custom

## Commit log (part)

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2023-11-16 Initial commit with clean KiCAD project
2023-11-17 DRAFT: schematics, initial PCB placement overview
2023-11-22 DRAFT:replace saml11 by stm32l412, add USB
2023-11-30 rename to iot-risk-logger-stm32l4 and andd harwware/
2023-11-30 CubeMX: initial project
2023-11-30 CubeMX: draft initial config, KiCad: pins assignment draft
2023-12-03 CubeMX: set pins
2023-12-08 CubeMX: add qspi
2023-12-12 PCB: first version of layout
2024-01-21 Schematics: assign all BOM parts
2024-01-24 PCB: prefinal board
2024-01-25 PCB: prefinal static routing
2024-01-25 PCB: routed
2024-01-25 BOM: export and cleanup
2024-01-27 README: add dev tools table
2024-01-28 README: add hw specs
2024-01-28 README: update schematics
2024-01-28 README: add drawing
2024-02-07 PCB: paint in different colours
2024-06-22 PCB: add colours and board extraction cutout
2024-06-27 :truck: refactor(CubeMX) tick .c & .h to place together
2024-06-27 :feat: feat(info LED) create a helloworld LED blinking task
2024-06-27 :wrench: feat(NFC) configure X-CUBE-NFC in CubeMX for custom board
2024-06-27 :star::wrench: feat(NFC) add super basic NFC init attempt, wipe out nfc_lib
2024-06-29 :heavy_plus_sign: add hardware-debu/ folder with debug probes projects
2024-06-30 :star: feat(NFC) basic NFC init, flash LED on GPO interrupt
2024-07-02 :star: feat(RTT) add debug SEGGER RTT library, tweak NFC init sequence
2024-07-02 :shirt: refactor(NFC) split NFC to task and ST25DV handlers
2024-07-02 :star: feat(NFC) draft read MB length, MB data to buffer, buffer debug printf
2024-07-17 :construction: feat(Actors) add basic actor model capability, Actor base struct
2024-07-18 :construction: new(temperature-humidity sensor) add TH Sensor initial task structure
2024-07-18 :shirt: refactor(NFC) migrate to Actor model
2024-07-18 :arrow_up: deps(sht3x) add senserion sht3x sensor library
2024-07-28 :construction: feat(TH Sensor) draft sht3x library integration
2024-07-28 :hatching_chick: feat(Light Sensor) initial files infrastructure
2024-07-29 :star: feat(Light Sensor) initial task's infrastructure
2024-07-30 :start: feat(OPT3001) Driver
2024-07-30 :start: feat(OPT3001) Light Sensor init function
2024-07-30 :star: Light Sensor Single shot read
2024-07-31 :WIP: introducing gh-pages
2024-07-31 :WIP: feat(gh-pages) awesome theme
2024-08-04 :star: feat(Light Sensor) implement transition handlers, State diagram docs
2024-08-04 :star: feat(SHT3x) create drivers interface
2024-08-07 :arrow_up: deps(RTT, sht3x) get rid of
2024-08-07 :arrow_up: deps(SystemView) add library
2024-08-07 :heavy_plus_sign: update(FreeRTOS) apply patch for Segger SystemView support
2024-08-07 :arrow_up: deps(SEGGER RTT) add library
2024-08-07 :shirt: refactor(RTT) replace RTT printf by SystemView
2024-08-07 :star: feat(SystemView) add initial config
2024-08-08 :star: feat(Light Sensor) add simple log state transitions capability
2024-08-08 :shirt: refactor(core) nest basic folders under core/
2024-08-08 :hatching_chick: feat(CRON) set time/date to compile time/date
2024-08-09 :heavy_minus_sign: update(FatFS) remove, move dependencies to main.h, set unused pins analog
2024-08-09 :white_check_mark: ci(artifacts) add RAM/Flash usage CI, basic badges to README
2024-08-09 Update Flash and RAM usage artifacts
2024-08-09 deploy: 0c11e6981373df3ce91faa5968dac99d8ac4b417
2024-08-11 :construction: wip(cron) rtc events handle
2024-08-12 :arrow_up: deps(STM32Cube MCU Package) upgrade to 1.18.1
2024-08-12 :star: feat(INFO_LED) switch from task to non-task functionality
2024-08-12 :star: feat(STOP2) add simple LP mode enter, disable USB init
2024-08-12 :shirt: refactor(tasks) from dynamic to static
2024-08-12 :star: feat(retarget) proper fprintf utilization with SystemView debug printf
2024-08-13 :star: feat(stop2) fix sleep mode unexpected interrupts
2024-08-13 :hatching_chick: feat(memory) task initialization
2024-08-14 :hatching_chick: feat(power mode manager) initial creation
2024-08-14 :star: feat(event manager) add pub/sub on global events, actors global registry
2024-08-16 :star: feat(light sensor) integrate global init receive
2024-08-16 :construction: wip(th sensor) start implementing the interface functions
2024-08-17 :star: feat(th sensor) io init, crc8, ID read
2024-08-17 :star: feat(th sensor) implement continuous measurements
2024-08-19 :star: feat(i2c) add mutex so light and th sensors are not conflicting
2024-08-20 :hatching_chick: feat(w255q) driver initialization
2024-08-20 :pencil: docs(sensors) prettify FSM description
2024-08-20 :pencil: docs(sensors, memory) add some basic Doxygen comments to core handlers
2024-08-20 :lipstick: update(debug) printf on DEBUG defined
2024-08-29 :star: feat(w25q) basic driver implementation
2024-09-03 :construction: wip(storage) start implementing storage-usb middleware
2024-09-03 :star: feat(w25q) NOR flash driver finished
2024-09-06 :star: feat(FAT12) add static boot sector image
2024-09-06 :star: feat(memory) free space seek function
2024-09-28 :construction: wip(storage) writing th & lux measurements on their readiness
2024-10-04 :star: feat(MEMORY) add WakeUp, structure FAT12 flashing, feat(DEBUG) get rid of custom retarget
2024-10-05 :star: feat(MSD) update storage middleware so USB read wakes up W25Q flash
2024-10-07 :star: ferat(GPIO_EXTI) extract int callbacks to a separate module
2024-10-07 :package: deps(ST25FTM) add library to manage Mailbox transfers
2024-10-10 :construction: feat(NFC) add client-server protocol idea doc, FSM draft doc
2024-10-15 :construction: feat(NFC) implement basic FSM handlers drafts
2024-10-15 deploy: 02b98dc5e5bc3c590996b7484fe46ea373aad30d
2024-11-06 :construction: wip(MEMORY) implemented settings read/write flow
2024-12-11 :construction: feat(NFC) pass CMDs to event manager. :boom: hard faults on NFC settings read flow, for now
2025-09-24 :construction: wip(NFC) disable NFC to support chip removal
2025-09-25 :construction: wip(STOP2) return pre/post sleep processing with disabling the debugger
2025-09-25 deploy: 5b217efe0f567edaef182848e406f4c5bf5507b8
2025-10-04 :construction: wip(POWER) disabple perepherial on sleep
2025-10-04 deploy: 4a98efdf2b5086cfb1a20a7d54cd339277d02fda
2025-10-27 :construction: wip(SCH/PCB) draft schematics with STM32L433 and evolved power rails
2025-11-03 Initial plan
2025-11-03 Add comprehensive architecture review and code quality improvement templates
2025-11-03 Add implementation guide and executive summary for architecture improvements
2025-11-03 Add comprehensive review documentation with quick start guide
2025-11-06 :construction: wip(SCH/PCB) update schematics, pcb and generate fabrications
2025-11-16 :construction_worker: build(update gcc): from 10 to 14
2025-11-16 :sparkles: feat(SYSTEM): sensors I2C gatekeeper service
    A dedicated RTOS task (Actor) that serializes all I2C transactions.
    All modules submit I2C requests to this service via a message queue.
    This service is the only module that directly interacts with HAL I2C driver.
    It ensures bus arbitration, error recovery, and safe STOP2 low-power reinitialization.
    Task: DFT-21
    Task URL: https://www.notion.so/sparkles-feat-SYSTEM-sensors-I2C-gatekeeper-service-2ac109abe356800d9a3edb3c353fec86?source=copy_link
2025-11-16 feat(i2c): Add industry-standard error handling and bus recovery
    - Add retry logic for HAL_BUSY with configurable retries (default: 3)
    - Add bus error recovery using HAL_I2C_GetError() and bus reset
    - Add I2C_BusService_Reset() function for power management and recovery
    - Add configurable retry parameters (MAX_RETRIES, RETRY_DELAY_MS)
    - Remove incorrect stack allocation warning comment
    - Improve code documentation and inline comments
2025-11-16 test: Add Unity unit tests for I2C Bus Service
    - Set up Unity test framework infrastructure
    - Add comprehensive test suite for sensors_bus module
    - Tests cover: initialization, request handling, error recovery, reset
    - Add mock HAL and RTOS types for hardware-independent testing
    - Update CI workflow to run unit tests automatically
    - All 10 tests passing
2025-11-18 :star: feat(temperature sensor): increase init delay, few other chores
2025-11-18 :green_heart: ci(GH Actions): update CI script according to latest Github standard and split it to sub-scripts
2025-11-20 :sparkles: feat(IMU): add basic configuraton, initial data read on FIFO watermark and freefall events
2025-11-21 :bug:fix(IMU):i2c1 resource access initialization throughout mutex
2025-11-21 Fix FIFO processing bug: move return statement outside loop
2025-11-21 Integrate LIS2DW FIFO logging into memory pipeline
2025-11-21 Fix FIFO averaging to use actual samples read count
2025-11-21 :sparkles: feat(IMU):initialization, FIFO reading, data averaging and saving to memory on CRON
    DFT-27
    :sparkles: feat(IMU): add basic configuraton, initial data read on FIFO watermark and freefall events
    :bug:fix(IMU):i2c1 resource access initialization throughout mutex
    :sparkles:feat(IMU): add draft averaging on 16 samples ready, averaging on writing to memory on CRON
2025-11-21 deploy: f680d30fcd3bd6b1176ac6901b0616c463531824
2025-11-24 deploy: 0718ddfc33334b70ea9e23dacfabe74723f13a6c
2025-11-29 :sparkles: feat(NFC) settigns write
2025-11-29 refactor(NFC): Rewrite to synchronous POSIX-style API
    - Remove FSM states and async message handling
    - Add POSIX-style functions: NFC_Init(), NFC_Read(), NFC_Write()
    - Add CRC8 validation with NFC_ValidateCRC8() and NFC_ComputeCRC8()
    - Add NFC_BuildResponse() for protocol packet building
    - Implement synchronous command dispatch for all GLOBAL_CMD_*
    - Add direct flash read/write for settings and log chunks
2025-11-29 fix(NFC): Prevent double response for commands that send their own response
    Add NFC_OK_RESPONSE_SENT return code for handlers that already sent their
    response (read_settings, read_log_chunk). Main task loop now checks for
    this code to avoid overwriting data responses with empty ones.
2025-11-29 refactor(NFC): Address code review feedback for robustness
    - Add NFC_MAX_LOG_CHUNK_SIZE constant for buffer sizing
    - Use memcpy for safer little-endian address extraction
    - Document end-of-log detection (0xFF = erased NOR flash state)
2025-12-02 [DRAFT] CubeMX project regenerated
